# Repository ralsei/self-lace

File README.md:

# Self-lacing Shoe

My final project for Swartzendruber's Digital Electronics class in 2019, built w/ Skillet (https://github.com/killerskyman).
It's a shoe that ties itself.

## Render

.png)

## Licensing

It's under the BSD license with an additional clause stating that you can't use this for PLTW.

## Building

The CAD is made in Inventor, and the PCB is made in EAGLE.
To build the code, you must make the PCB as specified, bootload it, then upload code via FTDI.

Use the script `build` with the following parameters:

`./build main.ino <your TTY here>`

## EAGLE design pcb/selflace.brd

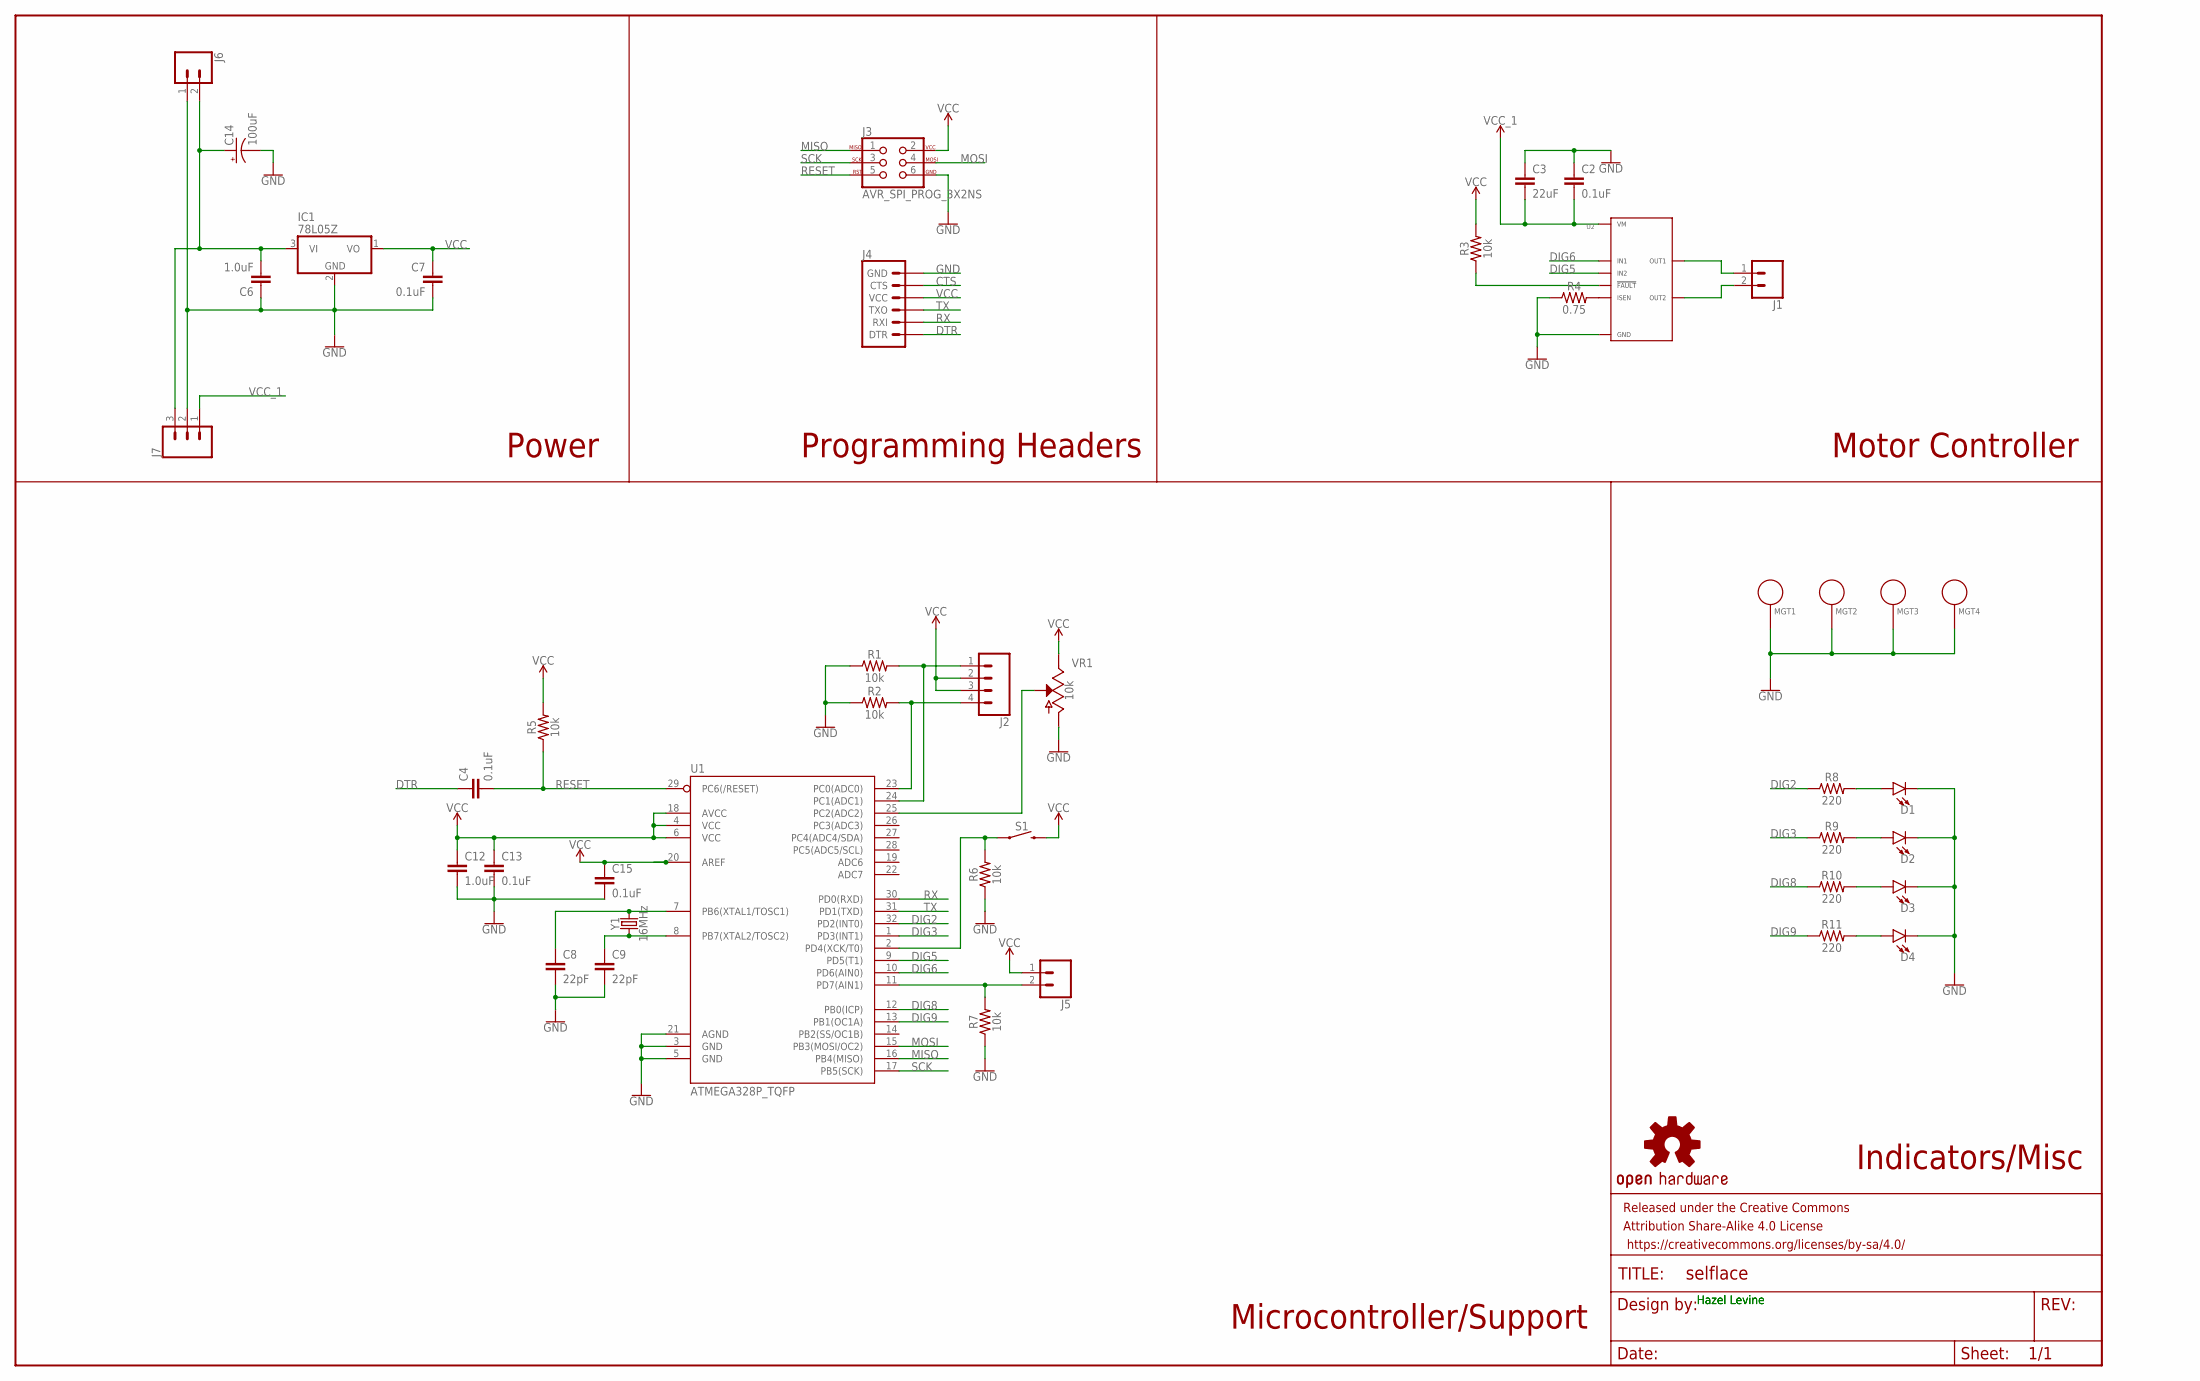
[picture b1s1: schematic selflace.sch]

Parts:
C2, C4, C7, C13, C15: 0.1uF; 0603
C3: 22uF; 0805
C6, C12: 1.0uF; 0603
C8, C9: 22pF; 0603
C14: 100uF; NIC_10X10.5_CAP
D1, D2, D3, D4: LED1206; LED-1206
FRAME1: FRAME-LEDGER; CREATIVE_COMMONS
IC1: 78L05Z; TO92
J1, J5: CONN_02; 1X02
J2: CONN_04; 1X04
J3: AVR_SPI_PROG_3X2NS; 2X3-NS
J4: 6_PIN_SERIAL_TARGETSILK; 6_PIN_SERIAL_TARGET_SIDE_W_SILK
J6: CONN_02JST-PTH-2; JST-2-PTH
J7: CONN_03; 1X03
LOGO1: OSHW-LOGOM; OSHW-LOGO-M
MGT1, MGT2, MGT3, MGT4: BEAGLEBONEBLACK_MOUNTING_HOLE
R1, R2, R3, R5, R6, R7: 10k; 0603
R4: 0.75; 0805
R8, R9, R10, R11: 220; 0603
S1: MOMENTARY-SWITCH-SPST-PTH-6.0MM; TACTILE_SWITCH_PTH_6.0MM
U1: ATMEGA328P_TQFP; TQFP32-08
U2: DRV8872DDARQ1; DRV8872_HSOP-8
VR1: 10k; POT-PTH-ALPS
Y1: 16MHz; CRYSTAL-SMD-5X3.2-4PAD

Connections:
CTS: J4.P$5 (CTS)
DIG2: R8.1, U1.32 (PD2(INT0))
DIG3: R9.1, U1.1 (PD3(INT1))
DIG5: U1.9 (PD5(T1)), U2.P$2 (IN2)
DIG6: U1.10 (PD6(AIN0)), U2.P$3 (IN1)
DIG8: R10.1, U1.12 (PB0(ICP))
DIG9: R11.1, U1.13 (PB1(OC1A))
DTR: C4.1, J4.P$1 (DTR)
GND: C2.1, C3.1, C6.1, C7.2, C8.2, C9.2, C12.2, C13.2, C14.-, C15.2, D1.C, D2.C, D3.C, D4.C, IC1.2 (GND), J3.6, J4.P$6 (GND), J6.1, J7.2, MGT1.P$1, MGT2.P$1, MGT3.P$1, MGT4.P$1, R1.1, R2.1, R4.1, R6.1, R7.1, U1.3 (GND), U1.5 (GND), U1.21 (AGND), U2.P$1 (GND), U2.P$9 (GND), U2.P$10 (GND), U2.P$11 (GND), U2.P$12 (GND), U2.P$13 (GND), U2.P$14 (GND), U2.P$15 (GND), VR1.P$3 (A)
MISO: J3.1, U1.16 (PB4(MISO))
MOSI: J3.4, U1.15 (PB3(MOSI/OC2))
unnamed: R6.2, S1.1, U1.2 (PD4(XCK/T0))
unnamed: J5.2, R7.2, U1.11 (PD7(AIN1))
unnamed: R3.1, U2.P$4 (!FAULT)
unnamed: J1.1, U2.P$6 (OUT1)
unnamed: J1.2, U2.P$8 (OUT2)
unnamed: U1.25 (PC2(ADC2)), VR1.P$2 (S)
unnamed: C8.1, U1.7 (PB6(XTAL1/TOSC1)), Y1.3 (2)
unnamed: R4.2, U2.P$7 (ISEN)
unnamed: J2.4, R2.2, U1.23 (PC0(ADC0))
unnamed: J2.1, R1.2, U1.24 (PC1(ADC1))
unnamed: C9.1, U1.8 (PB7(XTAL2/TOSC2)), Y1.1
unnamed: C6.2, C14.+, IC1.3 (VI), J6.2, J7.3
unnamed: D1.A, R8.2
unnamed: D2.A, R9.2
unnamed: D3.A, R10.2
unnamed: D4.A, R11.2
RESET: C4.2, J3.5, R5.1, U1.29 (PC6(/RESET))
RX: J4.P$3 (RXI), U1.30 (PD0(RXD))
SCK: J3.3, U1.17 (PB5(SCK))
TX: J4.P$2 (TXO), U1.31 (PD1(TXD))
VCC: C7.1, C12.1, C13.1, C15.1, IC1.1 (VO), J2.2, J2.3, J3.2, J4.P$4 (VCC), J5.1, R3.2, R5.2, S1.3 (2), U1.4 (VCC), U1.6 (VCC), U1.18 (AVCC), U1.20 (AREF), VR1.P$1 (E)
VCC_1: C2.2, C3.2, J7.1, U2.P$5 (VM)

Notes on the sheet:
Hazel Levine
Power
Microcontroller/Support
Programming Headers
Motor Controller
Indicators/Misc

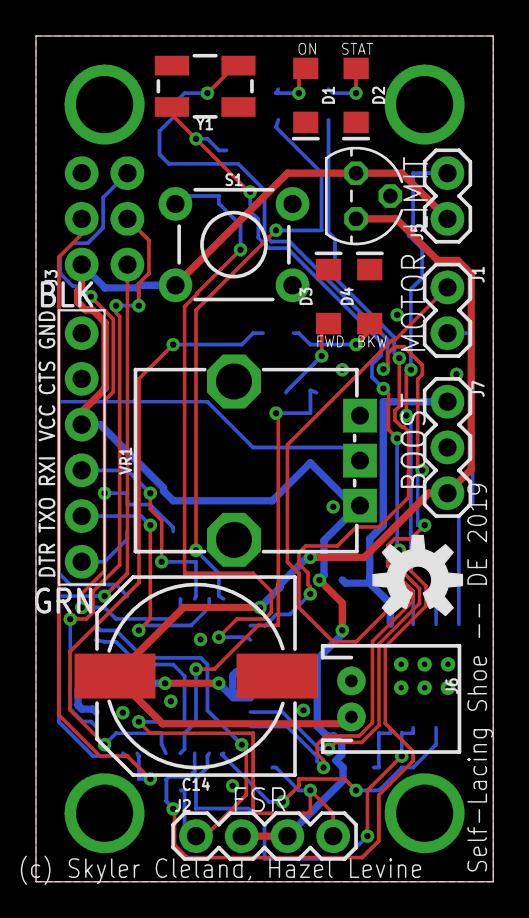
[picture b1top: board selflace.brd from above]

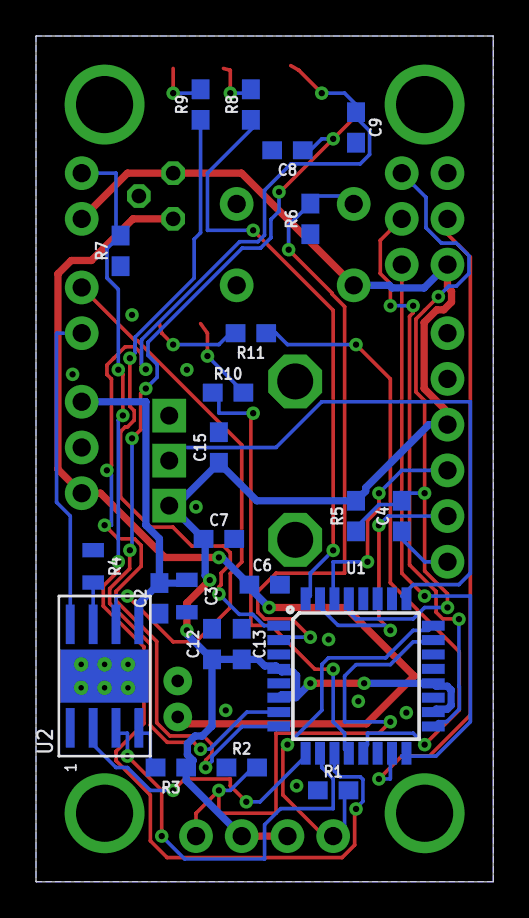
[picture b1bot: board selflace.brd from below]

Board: 2 copper layers, 25.4 x 47.0 mm, 45 parts (23 on the bottom side), 32 nets.

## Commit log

2019-05-09 init
2019-05-09 fix pcb, rewrite build script, move main
2019-05-10 sending sch off for review
2019-05-10 maybe finish schematic, sending off for review
2019-05-11 nearly done! sending off for final review
2019-05-12 add LEDs
2019-05-12 update board to size specs and increase power/ground trace width
2019-05-12 add sch border back, fix wire stubs
2019-05-12 fix some more wire stubs
2019-05-12 fix a thin ground trace
2019-05-12 routing is hell and i hate it
2019-05-12 yay, it's a thing that does a thing that's made to do a thing
2019-05-13 maybe final
2019-05-14 do some cleanup, remove half-h code
2019-05-21 add custom 3-clause bsd license
2019-05-21 instead of running indefinitely, set m_setpoint to 0 on ul
2019-05-21 Revert "update readme"
    This reverts commit 76895032cfc8c7d7bd5ceb4bf97c1fe1b72d243c.
2019-05-21 Revert "instead of running indefinitely, set m_setpoint to 0 on ul"
    This reverts commit d9a936486a13b2ac75d62348d48fa9a448d22195.
2019-05-21 fix rx/tx, not present on in-class pcb
2019-05-23 cad commit

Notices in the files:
parts and their libraries:
SparkFun-Capacitors: Licensing: Creative Commons ShareAlike 4.0 International - https://creativecommons.org/licenses/by-sa/4.0
SparkFun-Aesthetics: Released under the Creative Commons Attribution Share-Alike 4.0 License
SparkFun-Aesthetics: https://creativecommons.org/licenses/by-sa/4.0
